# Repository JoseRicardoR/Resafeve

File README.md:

# Resafeve
Proyecto final de Sistemas Embebidos Universidad Nacional de Colombia

**Toda la información de este proyecto se encuentra en el repositorio de github: https://github.com/esteban11519/SistemasEmbebidos**

Integrantes del grupo:
*Mateo Bernal Bonil - Valentine Chimezie Muodum Prieto - Esteban Ladino Fajardo - Jose Ricardo Rincón Peláez*

Se quiere hacer un sistema de monitoreo en reservas naturales para reservas naturales, en el cual se instalan microfonos en arboles para el regustro de audio y su procesamiento con IA en un servidor aparte. Los micrfonos se controlan con ESP32, la comunicación se plantea por medio de MQTT al servidor Mosquitto situado en una Raspberry, conectada tambien a un servidor online.
En el siguiente esquema se ve la logica de funcionamiento, aunque en nuestro caso se hace uso de un servidor Mosquito, y el sensor es un microfono. Además si bien se pueden recibir mensajes con el ESP32 (y además se implemento dicha función) no fue necesario una aplicación que usara ese camino.

Luego, la inteligencia artificial usada se encuentra en: https://github.com/IBM/MAX-Audio-Classifier . Además la ESP32 deberá correr un sistema operativo en tiempo real para su mejor rendimiento, en este caso se usa FreeRTOS.

El proceso planteado es el siguiente:
* Registrar alrededor de 10 segundos en un arreglo de bytes en el ESP32.
* Enviar la señal en bytes desde el ESP32 hasta la raspberry por medio de mqtt.
* Luego en la raspberry convertir los datos en bytes en un archivo de audio .wav.
* Procesar con la IA el archivo de audio y obtener los resultados.
* Guardar los resultados en la en la base de datos InfluxDB.
* Finalmente mostrar los resultados en una pagina web para la toma de decisiones.

En cuanto a este repositorio, el archivo README es una documentación extensa y detallada de lo desarrollado, y se encuentran cuatro carpetas con las partes del proyecto. La carpeta de "DockerServices" contiene todas las aplicaciones de Docker además de las herramientas necesarias, la carpeta "ESP32" contiene todos los archivos relacionados con el microcontrolador, la carpeta "Front_end" la infromación relacionada a la pagina web y la carpeta "Prototipo" la información relacionada con el producto fisico en cuestion.

## Funcionalidad de la ESP32
En la carpeta del "SistemasEmbebidos/ESP32/EjemplosGuia/" se encuentran los siguientes archivos que sirven como base para realizar pruebas sencillas y entender el manejo de las herramientas usadas:
* freeRTOS.ino, que es un codigo desarrollado en arduino para la ESP32 en el que se ejemplifica el uso del FreeRTOS con multiples tareas.
* esp32_Multitasking.ino, que es otro ejemplo del uso de FreeRTOS pero aprovechando los dos cores del ESP32.
* mqtt_ESP32.ino, es un ejemplo de uso de MQTT en el ESP32 para muestrar datos, publicarlos, y recibir información. Como servidor de prueba se usa test.mosquitto.org, que es gratuito y disponible en internet para todo publico.
* I2C_Mic.ino, es el codigo de prueba más sencillo posible el microfono INMP441 con la interfaz I2S en el ESP32.
* python_mqtt_client.py, es un script de python sencillo que recibe y publica mensajes por medio de MQTT. Este fue modificado para que cuando acabara de generar en .wav lo enviara a la inteligencia artificial y publicara los resultados en el tópico cuyo inicio es *Embebidos/* los cuales se guardaban en la base de datos InfluxDB. En última instancia se le cambió el nombre a app.py y se ejecutó en un docker.

El microcontrolador usado en el proyecto es el ESP32 de referencia Wemos Loolin32. Este dispositivo cuenta con dos cores y la posibilidad de conectarse a internet. 

Con el desarrollo del proyecto se evidenciaron y señalaron las limitaciones del dispositivo.

### PubSubClient
Para la comunicación se usa el protocolo de MQTT, que en el caso de la ESP32 se conecta con la librería PubSubClient, y para los demás elementos se usa la líbreria de python paho-mqtt. MQTT usa un sistema de subscripciones para la publiación de mensajes a tópicos específicos en el servidor.

Luego, unas primeras preguntas fueron ¿Cuantos segundos puede grabar el ESP32?¿De que tamaño es el Packete que se enviara?
De acuerdo a la documentación de pubsubclient el paquete máximo que se puede enviar son 256 bytes con la configuración. Es decir, hay un limite en el tamaño de paqute que se puede enviar, más en la propia documentación se explica que con la funcion client.setBufferSize(MQTT_MAX_PACKET_SIZE); se puede elegir el tamaño máximo del Buffer.
Luego la duda es por el lado de que tamaño es limite máximo que podemos tener. La cuestion es que entre más grande el paqute más se depende de la conexión a internet.

### Microfono electret
En primera instancia se probó para el muestreo de audio el uso de un micrófono electret con una configuración de amplifiación ya usada en otros proyectos. Luego el ESP32 en alguno de sus pines de lectura debería de ser capaz de muestrear la señal a la frecuencia deseada con el uso de un while y un delay. El archivo ESP32_Audio_mqtt_electret.ino en la carpeta del proyecto, se muestra el código en cuestion.

Cuando se implemento el codigo se encontró con el primer problema, la lectura de los pines del ESP32 no funcionaba. 
¿Por qué no funciona el AnalogRead en el código?
En cuanto al error de lectura del ESP32 cuando se usa el WiFi y MQTT el problema son que pines se eligen. Tal como indica la documentación y un foro, algunos Pines (como el 13 que se estaba usando) usan registros ADC2 que son los que manejan las funciones de WiFi de forma que si el WiFi esta activado quedan inhabilitados. Los pines que no se pueden usar son:  GPIO0, GPIO2, GPIO4, GPIO12 - GPIO15, GOIO25 - GPIO27. Luego de cambiar a los pines 34 para la lectura esta se hizo posible. 

Con el montaje inicial se desarrollo un script de python (en la carpeta SistemasEmbebidos/ESP32/Proyecto/python_mqtt_client_packages.py ) que recibia la información enviada del ESP32 y usaba multiples librerias. El proceso era:
* Se divide la información en el ESP32 en dos bytes por dato. La lectura es de 12 bits escalada a 16 bits. Pero el canal es de solo un byte de ancho. Además la inteligencia artificial pide idealmente un audio de 10s con una frecuencia de muestreo de 44100Hz y una resolución de 16 bits.
* En python se recibió esta información y con la funcion [numpy.frombuffer](https://numpy.org/doc/stable/reference/generated/numpy.frombuffer.html?highlight=frombuffer#numpy.frombuffer) se llega a la solución ya que retorna un arreglo unidimensional a partir de la señal de entrada 
* En el archivo python se usa luego la función numpy.concatenate para crear una [variable global](https://es.stackoverflow.com/questions/10768/crear-variables-globales-en-python) con toda la información recibida en todos los paquetes.  
* Finalmente se usan variables para contar los paquetes y datos y cuando se llega al punto deseado se usa https://docs.scipy.org/doc/scipy/reference/generated/scipy.io.wavfile.write.html#scipy.io.wavfile.write para crear el .wav

Este proceso funcionaba pero la calidad del sonido era mala y los tiempos de eran mucho más largos de lo esperado (enviar 9 segundos costaba casi minuto y medio). Una alternativa era usar las funciones beginplubish() y endpublish() de PubSubClient para que el proceso fuese más bien un stream de datos. Más sin embargo, estas dos funciones no enviaban toda la información por algún error desconocido. 

La solución inicial fue bajar la frecuencia de muestreo, de 44100Hz a 8000Hz. Antes de ello se probo en la inteligencia artificial que aún con audios de 8000Hz se obtuvieran resultados decentes. En comparación los resultados se muestran a continuación:
```
* 44100 Hz: {"status": "ok", "predictions": [{"label_id": "/m/01j4z9", "label": "Chainsaw", "probability": 0.6540094614028931}, {"label_id": "/m/04_sv", "label": "Motorcycle", "probability": 0.1308945119380951}, {"label_id": "/t/dd00066", "label": "Medium engine (mid frequency)", "probability": 0.12884050607681274}, {"label_id": "/m/0_ksk", "label": "Power tool", "probability": 0.11332365870475769}, {"label_id": "/m/07yv9", "label": "Vehicle", "probability": 0.10684427618980408}]}
```
```
* 8000 Hz: {"status": "ok", "predictions": [{"label_id": "/m/01j4z9", "label": "Chainsaw", "probability": 0.4117594063282013}, {"label_id": "/m/04_sv", "label": "Motorcycle", "probability": 0.206061452627182}, {"label_id": "/m/07yv9", "label": "Vehicle", "probability": 0.1337493658065796}, {"label_id": "/m/0_ksk", "label": "Power tool", "probability": 0.1071915328502655}, {"label_id": "/t/dd00066", "label": "Medium engine (mid frequency)", "probability": 0.07981646060943604}]}
```

Evidentemente con la frecuencia de muestreo mayor son mejores los resultados más con la frecuencia un poco más baja igual funciona.
Esto soluciono el problema del tiempo que ahora en total solo 16 segundos, es decir 2 segundos de envio por paquetes de 3 segundos. Paquetes mayores a 3 segundos con las condiciones descritas llenan la memoria. En términos generales se espera un tamaño de paquete alrededor de 48000 bytes. 
Por otro lado el problema de la calidad del audio seguia existiendo. Se probaron entonces mejores etapas de amplifiación como las mostradas en las imagenes.

Pese a esto el montaje mostrado en la siguiente figura no tenia una buena calidad de sonido, además de tener una frecuencia de muestreo baja.
Montaje con amplificación y micrfono electret.

En todo caso no se consiguio que la señal de audio fuera mejor, ni añadiendo condensadores de desacople, en su mayoria es ruido como se ve en la siguiente imagen. Por ende el sonido no es legible.

Se buscaron entonces alternativas y se encontro una de cambiar el sensor del proyecto.

### Microfono I2S INMP441
Tal parece que la conversión analoga digital del ESP32 consume mucho más CPU de la que se espera y hace que los procesos sean más demorados. Además si bien el circuito de amplificación está bien, se hace necesario el uso de un filtro para limpiar la señal. Se encontro que un micrófono Mems que usa la interfaz I2S se desarrollo para este tipo de proyectos. Su bloque funcional es como se ve a continuación.

Luego como ya todo esta incorporado en este micrfono la labor consiste en configurar el software para su buen funcionamiento. Al incio se obtuvo un problema visible en la imagen a continuación. 

El error consiste en que a veces el audio enviado no se graba correctamente, las muestras no se llenan por completo y hay muchos datos en 00. En consecuencia el audio suena entrecortado y “robótico”. Pese a las múltiples pruebas no he descubierto que genera estas inconsistencias, ni el tamaño ni cantidad de dma, ni los pines, ni el APLL-CLK, ni el tamaño de paquete ni audio total. Sencillamente, a veces funciona y a veces no.

Al revisar el montaje se encuentra que uno de los pines está mal conectado. Si se usa solo la señal mono izquierda es decir, .channel_format = I2S_CHANNEL_FMT_ONLY_LEFT,  se debe conectar el pin L/R a ground obligatoriamente. Dejarlo sin conectar como sugieren algunos tutoriales puede ocasionar el problema encontrado.

El montaje final es como se muestra a continuación. Muy sencillo.

El codigo completo se encuentra en la carpeta del proyecto con el nombre ESP32_I2S_Sampling.ino.
La señal de audio de salida es en definitiva clara y sin interrupciones. Se puede además muestrear a mayores frecuencias, se elige la de 16000Hz para no saturar de datos la red y la memoria del ESP32.

También se cambió el script de python para que ahora solo se requiera la libreria de Pahoo, así pues lo que se hace es generar un header al inicio del archivo que lo hace legible como .wav. Dicho header varia en relación a la frecuencia de muestreo, el numero de bits de resolución y el largo del archivo .wav.

El archivo definitivo tiene el nombre de ESP32_audio_receiver.py, y la explicación del header se puede encontrar en: http://soundfile.sapp.org/doc/WaveFormat/.

### FreeRTOS

En cuanto al componente FreeRTOS del proyecto, como se utiliza solo una función para todo el proceso en el ESP32, se procedio a hacer una tarea que contuviese todos estos elementos. En el archivo ESP32_I2S_Sampling.ino se ve como la tarea i2s_adc es instanciada como una task de FreeRTOS y este se reincia una vez cumple su ciclo. En una implementación donde se quisiese muestrear con dos microfonos al tiempo se podria crear una segunda tarea i2s_adc_2 con la misma funcionalidad. 

### Alimentación
Se analizaron dos alternativas para la alimentación de la ESP32 cuando se probase en campo. La primera y más sencilla es la alimentación de la tareta por medio de una pila de litio CR123 de 3.3V. En este caso se pudo realizar la prueba más parece para la aplicación dada se requiere una mayor potencia pues no fue suficiente para encender el montaje. Luego la segunda opción y mejor elaborada es el uso de paneles solares que carguen una pila de litio. Así será realmente independiente el diseño de estar conectado a una red electrica o de el recambio de baterias. El montaje es como se muestra a continuación y como documenta el proceso en https://randomnerdtutorials.com/power-esp32-esp8266-solar-panels-battery-level-monitoring/.

En la carpeta "Prototipo" se muestran imagenes de la PCB con todos los componentes mencionados, así como un imagen 3D de como se vería el montaje completo.

## Funcionalidad de la FPGA

La tarjeta FPGA usada para este proyecto es la Blackice MX. Este dispositivo cuenta con la posibilidad de ser programado mediante un entorno grafico llamado
Icestudio mediante bloques que representan los modulos que normalmente se insatancian al ser usado un lenguaje de descripción de hardware convencional
(Verilog o VHDL).

### Tareas
La tarea principal a realizar por la FPGA en este proyecto consiste en la deteccion de audios validos que puedan ser analizados por medio de una inteligencia artificial,
esto con el fin de no saturarla con muchas peticiones procedentes de varios microfonos. Para que un audio se considere como válido, un porcentaje arbitrario de las
muestras que conforman una grabación (este porcentaje es determinado por el diseñador), deberá superar un umbral de intensidad (tambien establecido por el diseñador),
esto con el fin de determinar que el audio en efecto si puede contener información relevante y no es simplemente silencio o ruido intermitente.

Como ya se mencionó el ESP32 enviará la información referente a la Raspberry por medio de un servidor MQTT. Esta información será enviada a la FPGA por medio de un protocolo
de comunicacion serial (SPI), para su análisis y posterior devolución de resultados. En esta aplicación la Raspberry sera el denominado "Maestro" y la FPGA el "esclavo" debido
a como se realizan las solicitudes y quien es quien necesita enviar los comandos para la correcta operación del módulo.

Para esta implementación se hara uso del bloque esclavo presente en una de las librerias de Icestudio.

Cada muestra de audio es representada por 2 Bytes de datos (16 bits), Sin embargo el bus de datos de este módulo es de 8 bits (que son recibidos serialmente desde el 
maestro y organizados en un registro propio del módulo). Por tanto se asignara 2 posiciones de memoria (2 registros de 8 bits mapeados en derterminadas direcciones de memoria),
a una muestra de audio en un instante. Para el envio de esta señal a la FPGA se cuenta con el bloque "SPI-cmd-regs" que se encargara de primero apuntar a la dirección de
alguno de los registros de la muestra instantanea y luego escribir el dato designado por el maestro, tambien es posible leer este dato en caso de que se requiera hacer alguna comparación (notese que se requerirá hacer dos veces este proceso para llenar totalmente los registros asignados a la muestra). 

### Control por SPI

### Lectura de muestra

Arriba se puede ver el control de las posiciones de memoria de todos los registros asociados a la FPGA junto al diagrama que hace posible la concatenanción para la creación de
la muestra instantanea.

Una vez cargado el valor de la muestra instantanea, el maestro dará la orden de comparar la muestra con el valor de intensidad umbral previamente establecido, en caso tal de
que la muestra tome un valor mayor al establecido el contador se incrementara, esta orden de comparación tambien incrementara un registro donde se llevara la cuenta de cuantos
datos han sido comparados y por tanto el total de muestras validas que se han leido hasta el momento.

### Bloque de Comparación

### Bloque de Conteo de Muestras

El programa cuenta tambien con una funcion de reseteo universal de registros asignado a una posición de memoria en caso tal de que el maestro por alguna razon quiera abortar o 
reiniciar el proceso

En algunas imagenes se han mostrados bloques cuya unica funcion es leer constantes asociadas a posiciones de memoria especificas y retornar booleanos que son asignados a una variable de control en funcion a si esta constante coreesponde a la posicion de memoria seleccionada en una anterior transaccion, dichos bloques son los encargados de seleccionar el registro desde donde se seleccionara la información que sera enviada en la proxima transaccion de SPI desde el esclavo al maestro.

### Ejemplo de bloque de lectura de comparacion de identificacion de posicion de memoria

Para la lectura de registros se hace uso de un codificador 16-4 junto a un multiplexor 16-1 de 8 bits, la tarea del codificador es cifrar una la posiciones de memoria a la que se apuntó, de manera que este dato cifrado es reconocido como la linea desde la que el multiplexor deberá leer la información asociada a la posicion de memoria y por tanto enviarla por el pin MOSI. En caso de que ningun registro sea seleccionado para lectura, o de que se seleccione uno inexistente, la informacion enviada en la proxima transaccion al SPI será FF.

### Bloque de lectura de registros del esclavo

El mapa de memoria detallado obviando las posiciones asignadas a las instrucciones de apuntado, lectura y escritura se muestra a continuación.
### Mapa de Memoria del esclavo
<ul>
<li> hx01: M16_1  (Byte mas significativo de la muestra) </li>
<li> hx02: M16_2  (Byte menos significativo de la muestra) </li>
<li> hx03: Comparacion  (Emite un pulso que luego debera ser bajado a 0,
este pulso da la orden de comparar la muestra con el umbral y contabilizar) </li>
<li> hx04: U_Reset  (Resetea los contadores, hace la funcion de reset universal) </li>
<li> hx05: CriterioAud (Informa si las muestras que se han analizado superan  
el umbral de audio valido) </li>
<li> hx06: LCompleta (Informa si ya se ha hecho la lectura de todas las muestras) </li>
<li> hx07: Ndato1 (Recoge los 8 bits menos significativos de la cantidad total de 
datos que han sido leidos) </li>
<li> hx08: Ndato2 (Recoge los segundos 8 bits menos significativos de la cantidad
total de datos que han sido leidos) </li>
<li> hx09: Ndato3 (Recoge el bit mas signicado de la cuenta total de datos, este 
bit sera el menos significativo del arreglo de 8 bits que se envia) </li>
<li> hx0A: CUmbral1 (Recoge los 8 bits menos significativos de la cantidad total de 
muestras que han superado el umbral) </li>
<li> hx0B: CUmbral2 (Recoge los segundos 8 bits menos significativos de la cantidad
total de muestras que han superado el umbral) </li>
<li> hx0C: CUmbral3 (Recoge el bit mas significativo de la cantidad total de 
muestras que han superado el umbral,este bit sera el menos significativo del 
arreglo de 8 bits que se envia) </li>
</ul>

El diagrama total de la implementación de las funciones de comunicación (apuntado, lectura y escritura), y del esclavo (comparación, conteo, etc) se muestra a continuación.

### Diagrama de Implemantacion en la FPGA

Se adjunta a la documentación un archivo .ino haciendo las veces de maestro donde se puede verificar algunas de las funciones implementadas en la FPGA 
## Funcionalidad DockerServicios

Se encuentra implementado para la arquitectura ARMv7 y para AMD hasta antes de la integración total con el ESP32. En general los siquientes comandos se usan para ambas arquitecturas:

* Hacer una imagen (no olvidar estar en el directorio del Dockerfile y el punto al final):
```bash
sudo docker build -t <nombre_imagen>:tag . 
```
* Para montar servicios desde docker compose (se debe estar en el directorio del archivo *docker-compose.yml*):
```bash
sudo docker-compose up -d 
```

* Ver servicios montados:

```bash
sudo docker ps 
```

* Para reiniciar los servicios de docker compose (útil cuando se hace algún cambio en volúmenes y se debe estar en el mismo directorio del archivo docker-compose.yml).

```bash
sudo docker-compose restart 
```

* Para parar y eliminar los servicios de docker compose:
```bash
sudo docker-compose down 
```
* Para mirar las imágenes creadas:
```bash
sudo docker images
```

* Para eliminarlas:
```bash
sudo rmi <id/name>
```

Se eligió montar todos los servicios en contenedores docker dada la portabilidad.
### Servicios implementados en Docker

Se tomaron los mismos servicios que Sánchez [Sanchez] y las mismas configuraciones con algunas excepciones que se van a explicar.

#### Docker-compose

En el curso introductorio del youtuber [Pelado Nerd](https://www.youtube.com/watch?v=CV_Uf3Dq-EU) sobre docker se comenzó a montar contenedores desde comandos básicos hasta el punto de usar docker compose. Docke-compose hace parte de docker y su principal ventaja radica en organizar los volúmenes, las dependecias, los puertos y demás cosas en un archivo con el nombre *docker-compose.yml* de manera organizada. Sin embargo, la principal característica es que se crea por defecto una red entre los sevicios y el nombre de cada servicio tiene el alias de la ip de cada contenedor. Por ejemplo, en la siguiente sección de *docker-compose.yml* el Broker MQTT tiene la ip en el alias *mosquitto*.

```yml
services:
    mosquitto:
        image: eclipse-mosquitto:2.0.10
```

Esto es necesario dado que los contenedores pueden cambiar la ip y no se hace práctico en un proyecto dado que generaría fallas de comunicación.
#### Broker MQTT

Para este servicio se eligió mosquitto y esta es su configuración en docker compose:
```yml
mosquitto:
        image: eclipse-mosquitto:2.0.10
        restart: always
        ports: 
            - 1883:1883  
        volumes:
            - ./BaseDatos/mosquitto/config:/mosquitto/config
            - ./BaseDatos/mosquitto/data:/mosquitto/data
            - ./BaseDatos/mosquitto/log:/mosquitto/log
    
```

 1. image: eclipse-mosquitto:2.0.10
 
  Se elige una imagen de [Docker Hub](https://hub.docker.com/_/eclipse-mosquitto) con el tag 2.0.10 y se verifica que esté disponible para la arquitectura deseada que en este caso es AMD y ARMv7. 

2. restart: always

Esto permite que funcione cada vez que se prende el dispositivo que lo contiene o cada vez que tenga un error.

3.  
```yml
        ports: 
            - 1883:1883 
```

Se mapea el puerto interno del docker :1883 al puerto externo del dispositivo 1883:.

4. Volumes: el único que en realidad es importante es la configuración que hay en el archivo mosquitto.config y que se coloca en el directorio local ./BaseDatos/mosquitto/config que se va reflejar en el archivo con el mismo nombre dentro de la dirección del contenedor /mosquitto/config. Esto permite que cada vez que se reinicialice el docker se mantenga la misma configuración. El contenido de dicho archivo es:

```
listener 1883 0.0.0.0
allow_anonymous true
```
Recomentaciones:
- Debe recordarse que toda información que se coloque en un docker se va a eliminar una vez se reinicialice y por ende se deben colocar volúmenes para que esta sea persistente. Un error que se tuvo fue el pensar que si se configuraba el archivo desde el interior del contenedor el cambio en el volumen se iba a ver de manera local en el reinicio pero en realidad sucede lo contrario.

#### InfluxDB

Se escoge una base de datos de serie temporal dada la naturaleza del proyecto.

```yml
influxdb:
        image: influxdb:1.8
        restart: always
        ports: 
            - 8086:8086
        volumes: 
            - ./BaseDatos/influxdb_data:/var/lib/influxdb
        environment: 
            - INFLUXDB_DB=embebidos
            - INFLUXDB_ADMIN_USER=admin
            - INFLUXDB_ADMIN_PASSWORD=admin
            - INFLUXDB_HTTP_AUTH_ENABLED=true
```
1. ```image: influxdb:1.8```

Se elige la imagen *influxdb* con el tag *1.8* y se verifica en [Docker Hub](https://hub.docker.com/_/influxdb) la compatibilidad de arquitecuras. Se eligió otro tag con el objetivo de usar uno más actualizado pero se encontró que no se podía acceder a ella con el método que decía Sánchez y que se expone a continuación:

Para acceder al interior del contenedor InfluxDB se hace así:
```bash
sudo docker exec -it <id/nombre contenedor InfluxDB> bash
```
Registrarse con el usuario y contraseñas

```bash
influx -username <usuario> -password <contraseña>
```

Observar las bases de datos creadas
```bash
show databases
```
Usar una base de datos:

```bash
use <base de datos>
```
Mirar las distintas 'tablas' creadas:
```bash
show measurements
```

Observar todos los resultados de la tablas:
```bash
select * from <tabla>
```
Esto fue de ayuda para verificar que se estaban guardando los datos de manera correcta cuando no se tenía una interfaz gráfica. 

2. 
```yml
 ports: 
            - 8086:8086
```
Se mapeo el puerto :8086 del contenedor al puerto 8086: del dispositivo local.

3. 
```yml
        volumes: 
            - ./BaseDatos/influxdb_data:/var/lib/influxdb
```
Se guarda la información de la base de datos dentro de la ruta /var/lib/influxdb que está en el contenedor a la ruta local ./BaseDatos/influxdb_data. En este caso es como si hubiera un enlace simbólico del interior del contenedor al directorio local.

4. 
```yml
        environment: 
            - INFLUXDB_DB=embebidos
            - INFLUXDB_ADMIN_USER=admin
            - INFLUXDB_ADMIN_PASSWORD=admin
            - INFLUXDB_HTTP_AUTH_ENABLED=true
```
Se expecifica por medio de variables de entorno propios de esta imagen que la base de datos se llama *embebidos* (INFLUXDB_DB=embebidos), se coloca como usuario y contraseña *admin* (INFLUXDB_ADMIN_USER=admin, INFLUXDB_ADMIN_PASSWORD=admin) y se habilita la comunicación HTTP (INFLUXDB_HTTP_AUTH_ENABLED=true).

#### telegraf

Con este servicio se busca enviar toda la información publicada en un tópico configurado a la base de datos influxdB
```yml
telegraf: 
        image: telegraf:1.18.3
        restart: always
        volumes:
            - ./BaseDatos/telegraf/telegraf.conf:/etc/telegraf/telegraf.conf
        depends_on: 
            - influxdb
    
```
1. ```image: telegraf:1.18.3```: Se busca en [docker hub](https://hub.docker.com/_/telegraf) la imagen compatible con las arquitecturas.

2. 
```yml
volumes:
            - ./BaseDatos/telegraf/telegraf.conf:/etc/telegraf/telegraf.conf
```
El archivo de la ruta local ./BaseDatos/telegraf/telegraf.conf se vincula con el archivo dentro del contenedor /etc/telegraf/telegraf.conf y este es su contenido fundamental (lo que no significa la falta de la demás configuración):

```
[[outputs.influxdb]]
urls = ["http://influxdb:8086"]
database = "embebidos"
skip_database_creation = true
username = "admin"
password = "admin"
```
* La ip de la base de datos y el puerto está representado por http://influxdb:8086 que corresponde al alias de la base de datos InfluxDB y el puerto interno 8086 del contenedor.
* Se especifica que la base de datos que se va a usar es *embebidos* que debe coincidir con la creada en InfluxDB.
* No se crea nueva base de datos de datos.
* Se le coloca el mismo usuario y contraseña usados en las variables de entorno de InfluxDB.

```
[[inputs.mqtt_consumer]]
 servers = ["tcp://mosquitto:1883"]
 topics = ["Embebidos/#"]
     name_override = "embebidos"

    json_string_fields = [
      "predictions_0_probability",
      "predictions_1_probability",
      "predictions_2_probability",
      "predictions_3_probability",
      "predictions_4_probability"
      ]
      
    tag_keys = [
      "predictions_0_label",
      "predictions_1_label",
      "predictions_2_label",
      "predictions_3_label",
      "predictions_4_label"
      ]
    data_format = "json"
```

* Se especifica el protocolo de comunicación TCP, la dirección ip *mosquitto* y el puerto (1883) correspondientes al Broker MQTT.

* Se va a guardar en la base de datos influxDB la información que se publique en el tópico *Embebidos/#*
* Se especifica el nombre de la "tabla" (embebidos) en el que se va a guardar la información.
* Dada la estructura del json que se expuso anteriormente se escoge la información que se va a guardar que en este caso es el label y la probabilidad de ocurrencia asociada con dicho label.
* Finalmente se especifica que se va a guardar como un json (Se hace distinto que Sánchez [Sanchez].

Este último tema fue el que más causó dificultades dado que solo se estaban guardando las probabilidades más no los labels asociados. Para esto se buscó en la documentación de telegraf con respecto a los [tipos de datos json](https://github.com/influxdata/telegraf/tree/master/plugins/parsers/json) y se implementaron. Se notó que telegraf solo guarda datos que tengan la estructura configurada, esto generó un problema de comprobación en donde se enviaban datos con estructuras distintas y no se guardaban.

3.  
```yml
depends_on: 
            - influxdb
```
Se espera hasta que el servicio con nombre influxdb se haya creado para este hacerlo. Esto ayuda a que la base de datos de la configuración ya se haya creado.

#### grafana

Para realizar gráficos con respecto a la información que se tenga en la base de datos InfluxDB se usa Grafana. 
```yml
grafana: 
        image: grafana/grafana:7.5.7 
        restart: always
        ports:
            - 3000:3000 
        volumes:
            - grafana-storage:/var/lib/grafana  
        depends_on: 
            - influxdb
    
```

1. ```image: grafana/grafana:7.5.7```

Se busca una imagen compatible con las arquitecturas que se tienen en [Docker Hub](https://hub.docker.com/r/grafana/grafana)

2. 
```yml
        ports:
            - 3000:3000 
```
Se mapea el puerto :3000 del contenedor al puerto 3000: del dispositivo local.

3. 
```yml
volumes:
    - grafana-storage:/var/lib/grafana  
```

Se guarda de manera local en el volumen *grafana-storage* la configuración hecha en el contenedor para graficar los datos que se localiza en su ruta /var/lib/grafana.

4. 
```yml
volumes:
    grafana-storage:
        external: false
```
Se tuvo que crear un volumen *especial* para grafana porque fue la única forma que se encontró para que no se borraran los cambios editados en su interfaz después de varios intentos mediante la forma convencional con la que se venía haciendo.

#### ser_brokerconection

Este fue el servicio que se creo de manera local y cuya estructura varía un poco con respecto a las que se se expusieron. Su función principal es ejecutar de manera automática y continua el script ```app.py```.
```yml
    ser_brokerconection:
        build: ./BrokerMqttPython/BrokerConection
        restart: always
        depends_on:
            - mosquitto
```
1. build: ./BrokerMqttPython/BrokerConection

En la dirección relativa *./BrokerMqttPython/BrokerConection* al archivo docker-compose.yml se tiene una archivo Dockerfile que crea una imagen con la siguiente descripción:

```Dockerfile
FROM python:3.7.3

WORKDIR /usr/src/app

COPY requirements.txt ./
RUN pip install --no-cache-dir -r requirements.txt
RUN apt update && apt install -y curl && apt install -y avahi-daemon

COPY . .

CMD ["python3", "./app.py" ]
```
a.  ```FROM python:3.7.3```

Se descarga de Docker Hub la imagen python:3.7.3 que corresponde a la misma versión con el que se comprobó el correcto funcionamiento del script *app.py* en la raspberry.

b. ```WORKDIR /usr/src/app```

Establece el directorio de trabajo como /usr/src/app según la documentación de [Docker Hub](https://hub.docker.com/_/python). Esto significa que los cuando se increse al contenedor por medio de bash o cuando se copia (por comando del Dockerfile) algo dentro del contenedor se va a realizar en esta dirección.

c. ```COPY requirements.txt ./```

Copia el archivo requirements.txt que contiene las librería necesarias para el script *app.py* y que se encuentra en la misma dirección del archivo *Dockerfile* en el directorio de trabajo dentro del contedor.

d. ```RUN pip install --no-cache-dir -r requirements.txt```

Se instalan las librerías que están en requirements.txt.

e. ```RUN apt update && apt install -y curl && apt install -y avahi-daemon```

Se instala curl y avahi-daemon necesarios para el funcionamiento de *app.py*. Sin embargo, avahi-daemon no reconoció la ip de un dispositivo externo al que contenía el docker. Dada esta irregularidad se tuvo que colocar la ip numérica del dispositivo en el que se tiene el servicio de la IA.

f. ```COPY . .```

Se copia todo lo que hay en el directorio actual dentro del directorio de trabajo del Docker (excepto lo que está en .dockerignore).

e. ```CMD ["python3", "./app.py" ]```

Se ejecuta dentro del contenedor el comando ```python3 app.py``` por defecto.

2.  ```restart: always```

Se reinicia siempre y se crea después del servicio moquitto.

#### docker-compose final 

Uniendo todos los servicios en un docker-compose.yml se tiene el siquiente archivo:

```yml
version: '3.1'

services:
    mosquitto:
        image: eclipse-mosquitto:2.0.10
        restart: always
        ports: 
            - 1883:1883  
        volumes:
            - ./BaseDatos/mosquitto/config:/mosquitto/config
            - ./BaseDatos/mosquitto/data:/mosquitto/data
            - ./BaseDatos/mosquitto/log:/mosquitto/log
    
    telegraf: 
        image: telegraf:1.18.3
        restart: always
        volumes:
            - ./BaseDatos/telegraf/telegraf.conf:/etc/telegraf/telegraf.conf
        depends_on: 
            - influxdb

    influxdb:
        image: influxdb:1.8
        restart: always
        ports: 
            - 8086:8086
        volumes: 
            - ./BaseDatos/influxdb_data:/var/lib/influxdb
        environment: 
            - INFLUXDB_DB=embebidos
            - INFLUXDB_ADMIN_USER=admin
            - INFLUXDB_ADMIN_PASSWORD=admin
            - INFLUXDB_HTTP_AUTH_ENABLED=true
            
    grafana: 
        image: grafana/grafana:7.5.7 
        restart: always
        ports:
            - 3000:3000 
        volumes:
            - grafana-storage:/var/lib/grafana  
        depends_on: 
            - influxdb
           
    ser_brokerconection:
        build: ./BrokerMqttPython/BrokerConection
        restart: always
        depends_on:
            - mosquitto

volumes:
    grafana-storage:
        external: false
```
#### Inteligencia Artificial

La [inteligencia artificial](https://www.google.com/url?q=https://github.com/IBM/MAX-Audio-Classifier) se tiene implementada en una arquitectura AMD y puede reconocer los sonidos de este [archivo](./docs/class_labels_indices.csv) entre los cuales se encuentra motosierra, motor, vehículo, motocicleta y entre otros. Se obtienen 5 resultados numerados del 0 al 4 con sus repectivas probabilidades. Con el siguiente comando se obtienen de manera local los resultados:

```bash
curl -F "audio=@<dirección y extensión del audio>;type=audio/wav" -XPOST <Ip y puerto de la IA>/model/predict
```
Esta información se almacena en un archivo y se envía a la base de datos por medio del script app.py implementado en Docker.

#### Recomendaciones

La ip del servidor que contenga la IA se debe modificar en el archivo app.py y luego ejecutar el archivo docker-compose para la arquitectura arm.
## FRONT END
Para el front end (Interfaz Hombre Maquina) se realizó una página web que hace uso de lenguaje HTML, JAVASCRIPT, NODE.js, CSS y PYTHON para su funcionamiento como diseño. Particularmente NODE.js y PYTHON se uso para parte del backend que principalmente es la lectura de la base de datos InfluxDB. Para hacer una descripción de cada parte de la página clara y concisa se dividió la página en "Encabezado" y "Main".

### ENCABEZADO
Para el encabezado se siguió la siguiente maqueta de HTML.
```html
nav class="navbar">
        <div class="navbar_container">
            <a href="/" class="" id="navbar_logo"><i class="fab fa-pagelines"></i>Resafeve</a>
        </div>
        <div class="navbar_containerlinks">
            <ul class="navbar_menu">
                <li class="navbar_items">
                    <a href="https://github.com/esteban11519/SistemasEmbebidos" class="navbar_links">Documentacion</a>
                </li>
                <li class="navbar_items">
                    <a href="/" class="navbar_links">Equipo</a>
                </li>
                <li class="navbar_button">
                    <a href="http://192.168.1.86:3000/d/MZVyWBmRk/embebidos?from=1629944777057&to=1630549577057&orgId=1" class="button">Monitorear</a>
                </li>
            </ul>
        </div>
    </nav>
```

En el anterior código vemos varios elementos \<a> que hacen referencia a los "Links" a otras páginas. Para este caso tenemos los siguientes botones. 

Que como vemos en la maqueta de HTML al presionar "Documentacion" nos redirecciona al GitHub del proyecto mientras que al presionar Monitorear nos direcciona a Grafana a un Dashboard. Además de estos elementos tenemos los títulos de la página que tiene un estilo particular ya que se le agrego un degrade en la hoja de estilos. Además para el "icono" se uso un script prestado por la página https://fontawesome.com/, donde al registrarse y poner la etiqueta del script que nos dan para nuestra cuenta ya con solo hacer referencia a la clase "fab fa-pagelines" de la imagen esta aparece en el elemento deseado.

```css 
 #navbar_logo {
    background-color: #0a8124;
    background-image: linear-gradient(to bottom, #19e946 0%, #00a524 100%);
    background-size: 100%;
    -webkit-background-clip: text;
    -moz-background-clip: text;
    -webkit-text-fill-color: transparent;
    -moz-text-fill-color: transparent;
    display: flex;
    cursor: pointer;
    text-decoration: none;
    font-size: 2rem;
} 
        
```
Hay algunos otros elementos y utilidades de CSS que son interensantes, como el HOVER que nos permite interactuar con los elementos, como ponerlos opacos o cambiarlos de color. Esto hace la experiencia de usuario mucho mas amena.
        
### MAIN
        
Para el main se uso un contenedor que cotiene una imagen con una frase y adicionalmente tiene algunos widgets para la visualización de la información obtenida a su vez con la base de datos. Para el primer widget se uso programó un reloj con fecha mediate el usod de variables propias de javascript Date() y mediante a una iteración se actuliza la fecha y la hora por cada intérvalo de tiempo. Adicionalmente se programó un indicador de alarma basado en la última lectura de la base de datos y algunos criterios que se especificarán posteriormente. Este widget cambiará su color y su texto dependiendo del dato almacenado por el análisis de la inteligencia artificial.

 Ahora este Widget resume todo el funcionamiento principal del backend. Primero tenemos una aplicacion de Python la cual cuenta con la libreria mas importante para la lectura de datos desde la base de datos influxDB (INFLUXDB). Esta libreria nos permite crear un cliente y  conectarnos a la base de datos, para posteriormente usar la funcion .query para hacer solicitudes tipo "SQL". 

```py 
        client = influxdb.InfluxDBClient(host='192.168.1.86', port=8086, ....)
        Lecturas_2 = client.query(f"SELECT * FROM embebidos WHERE time > now()-14d")
```
De esta manera se crea un archivo json que posteriomente nos permite usar Node.js junto con algunos paquetes como  EXPRESS, CORS y FS. Estas librerías primero como EXPRESS sirven para montar servicios para hacer solicitudes APIS , CORS soluciona un problema de comunicación entre HTTPS y HTTP. Además, FS nos ayuda a leer los json. Finalmente con ayuda de FETCH se hace la solicitud desde la pagina web y mediante el metodo .then() podemos enviar los resultados retornados por FETCH a alguna función para de esta manera analizar y modificar el widget en cuestión.
 
```py 
     fetch('http://localhost:1500')
    .then(response => response.json())
    .then(data => printIt(data));
```

## Bibliografia
Recursos adicionales
* MQTT - Resumen de todo con explicaciones y links de temas relacionados: https://aprendiendoarduino.wordpress.com/2018/11/19/mqtt/ 
* Esp32 Mqtt explicado: https://randomnerdtutorials.com/esp32-mqtt-publish-subscribe-arduino-ide/
* Inteligencia Artificial que clasifica los sonidos: https://www.google.com/url?q=https://github.com/IBM/MAX-Audio-Classifier&sa=D&source=editors&ust=1630442220276000&usg=AOvVaw06XKVdFrBWjtAnfdxmKH8F 
* Documentacion Espressif del ESP32: https://docs.espressif.com/projects/esp-idf/en/latest/esp32/index.html
* Datasheet del Microfono INMP441: https://www.google.com/url?q=https://invensense.tdk.com/wp-content/uploads/2015/02/INMP441.pdf&sa=D&source=editors&ust=1630447016673000&usg=AOvVaw1flXUa5FAnurC2niqlp07R
*  Documentacion SPI y Icestudio: https://github.com/Obijuan/Cuadernos-tecnicos-FPGAs-libres/wiki/CT.5:-SPI-esclavo

* [Sanchez] J. J. Sánchez Hernández, «IoT Dashboard - Sensores, MQTT, Telegraf, InfluxDB y Grafana». may 20, 2021. [En línea]. Disponible en: http://josejuansanchez.org/iot-dashboard/

* «Docker Hub». https://hub.docker.com/ (accedido sep. 02, 2021).
Pelado Nerd, DOCKER 2021 - De NOVATO a PRO! (CURSO COMPLETO), (2021). Accedido: sep. 02, 2021. [En línea Video]. Disponible en: https://www.youtube.com/watch?v=CV_Uf3Dq-EU

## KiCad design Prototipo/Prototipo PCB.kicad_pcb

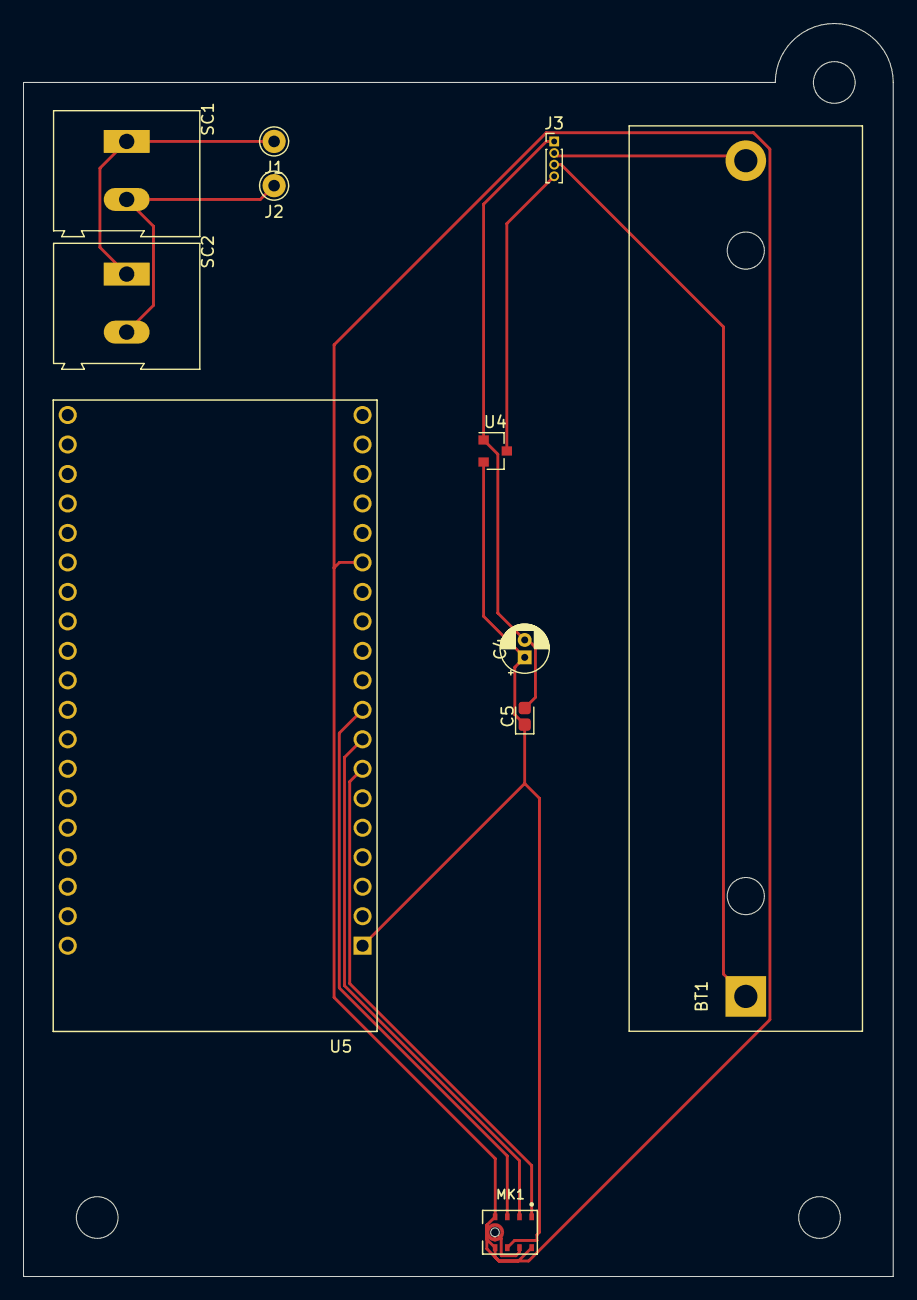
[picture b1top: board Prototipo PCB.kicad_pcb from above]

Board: 2 copper layers, 74.9 x 108.0 mm, 11 parts (0 on the bottom side), 11 nets.

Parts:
BT1: 3.7V; BatteryHolder_MPD_BH-18650-PC2
C4: 100uF; CP_Radial_D4.0mm_P1.50mm
C5: 100nF; CP_EIA-1608-08_AVX-J
J1, J2: Conn_01x01; Pin_D1.0mm_L10.0mm
J3: Conn_01x04; PinHeader_1x04_P1.00mm_Vertical
MK1: INMP441ACEZ-R7; MIC_INMP441ACEZ-R7
SC1, SC2: Solar_Cell; TerminalBlock_Altech_AK300-2_P5.00mm
U4: MCP1700-3302E_SOT23; SOT-23
U5: ESP32-DEVKITC-32D; MODULE_ESP32-DEVKITC-32D

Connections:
unnamed: BT1.1, J3.3
unnamed: BT1.2, J3.2
unnamed: C4.1, C5.1, MK1.7, U4.2, U5.1
unnamed: C4.2, C5.2, J3.1, U4.1
unnamed: J1.1, SC1.1, SC2.1
unnamed: J2.1, SC1.2, SC2.2
unnamed: J3.4, U4.3
unnamed: MK1.1, U5.7
unnamed: MK1.2, U5.8
unnamed: MK1.3, U5.9
unnamed: MK1.4, MK1.5, MK1.6, MK1.9, U5.14

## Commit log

2021-05-13 Base de datos lista en linuz con conexión a python
2021-05-15 Update esp32_Multitasking.ino
    Ejemplo de Multitasking y Multicore en el ESP32 con FreeRTOS
2021-05-27 Funciona la base de datos, el administrador phpmyadmin y la aplicación para buscar en la base de datos. Aparece el error del puerto 5000 ocupado
2021-05-29 Funciona la aplicación de manera automáttica
2021-05-31 Se implementó la base de datos con el servidor mosquitto
2021-06-01 Base de datos implementada con grafana
2021-06-04 Se publican en un broker-mqtt los resultados de la inteligencia artificial
2021-06-05 modificaciones leves
2021-06-06 arreglos
2021-06-14 se puso la base de datos en términos de variables de entorno
2021-06-17 Update mqtt_ESP32.ino
    el envio de datos ya es el correcto
2021-06-17 Add files via upload
    Cliente de python que se conecta con el ESP32, recibe sus datos y crea el .wav
2021-08-12 Rename esp32_Multitasking.ino to ESP32/esp32_Multitasking.ino
2021-08-12 Rename freeRTOS.ino to ESP32/EjemplosGuia/freeRTOS.ino
2021-08-12 Rename ESP32/esp32_Multitasking.ino to ESP32/EjemplosGuia/esp32_Multitasking.ino
2021-08-12 Rename mqtt_ESP32.ino to ESP32/EjemplosGuia/mqtt_ESP32.ino
2021-08-12 Rename python_mqtt_client.py to ESP32/EjemplosGuia/python_mqtt_client.py
2021-08-12 Rename ESP32/EjemplosGuia/AjusteMic.ino to ESP32/AjusteMic.ino
2021-08-12 Rename ESP32/EjemplosGuia/python_mqtt_client_packages.py to ESP32/Proyecto/python_mqtt_client_packages.py
2021-08-12 Rename ESP32/EjemplosGuia/ESP32_Audio_mqtt_Clean.ino to ESP32/Proyecto/ESP32_Audio_mqtt_Clean.ino
2021-08-12 Rename ESP32/AjusteMic.ino to ESP32/Proyecto/AjusteMic.ino
2021-08-15 Dos Docker pueden acceder a una misma carpeta
2021-08-18 Mejoras
2021-08-23 Se mejoraron los scripts de las bases de datos
2021-08-23 Base de datos arm
2021-08-24 Add files via upload
    Archivo de python que recibe señal del ESP32 y la convierte en .wav
2021-08-26 BrockerMqttPython en arm y telegraf guarda en string
2021-08-27 Organización
2021-08-27 configuración raspberry con aplicación paho.mqtt en docker
2021-08-29 Archivo funcional, para siempre de mqtt python
    Este archivo recibe los datos enviados por el ESP32 y los escribe en un .wav de nombre Audio, luego da 20 segundos despeus de recibir el ultimo paquete de datos para enviar o mover el archivo. Pasado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
2021-08-29 Archivo que corre el ESP32
2021-08-31 Update ESP32_audio_reciever.py
    Se agregaron los casos de error
2021-08-31 Rename ESP32_Audio_mqtt_Clean.ino to ESP32_Audio_mqtt_electret.ino
2021-09-01 Cambios telegraf
2021-09-01 Front-End files
2021-09-01 Mqtt
2021-09-01 audio
2021-09-01 Codigo HTML-CSS-JAVASCRIPT
    Front-End
2021-09-01 Rename ESP32_Audio_mqtt_electret.ino to ESP32_Electret_Sampling.ino
2021-09-01 Rename ESP32/Proyecto/AjusteMic.ino to ESP32/EjemplosGuia/AjusteMic.ino
2021-09-01 Update docker-compose.yml
    Prueba actulizacion docker compose
2021-09-02 Prueba 2
2021-09-02 Cambios amd
2021-09-02 Prueba ESP32
2021-09-02 Ras individual Broker
2021-09-02 Modificacion avahi
2021-09-02 Eliminación audios
2021-09-02 Update README.md
    Primera parte de Front-End
2021-09-02 Update README.md
    Actulizacion front-end
2021-09-02 Update README.md
    Actualizacion de Front End
2021-09-02 Update README.md
    Actualizacion
2021-09-02 Update README.md
    Actulizacion README.md
2021-09-02 Docker conexión actualizado
2021-09-02 Cambios raspberry
2021-09-02 Update README.md
    Mod
2021-09-02 Update README.md
    mods
2021-09-02 readme
2021-09-02 Esteban readme
2021-09-02 Después presentación
2021-09-02 Despues presentacion
2021-09-03 Modificación git
2021-09-04 Update README.md
    Readme actualuzado
2021-09-04 Add files via upload
    Docs
2021-09-04 Update README.md
    Readme actualizado
2021-09-04 Mod_web
    mod
2021-09-05 Página web
2021-09-05 Docker en arm de servicio web. Modificar index.js y app_1.js para docker
2021-09-05 cambio desde raspberry
2021-09-05 Update app_1.js
    mod
2021-09-05 cambios amd funciona pagina
2021-09-06 Funciona desde arm
2021-09-06 Add files via upload
    PDF 3d del prototipo
